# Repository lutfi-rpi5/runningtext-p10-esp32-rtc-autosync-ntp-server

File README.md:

# Running Text P10 ESP32 + RTC + Auto Sync NTP Server

**Detailed Engineering Design (DED) – Embedded System Engineer**

---

## 1. Tentang Sistem

Sistem ini adalah **Running Text LED P10 berbasis ESP32** yang dirancang sebagai papan informasi digital cerdas. Keunggulan utamanya adalah ketahanan terhadap gangguan internet: display tetap menampilkan teks berjalan dan waktu dari **RTC (Real-Time Clock)** meskipun jaringan Wi-Fi tidak tersedia. Ketika koneksi internet kembali, sistem akan **secara otomatis menyinkronkan waktu dari server NTP (Network Time Protocol)** dan menyimpannya ke modul RTC, memastikan akurasi waktu yang tinggi tanpa campur tangan pengguna.

Sistem dibangun dengan pendekatan **non-blocking** pada seluruh operasi (Wi-Fi, NTP, display), sehingga running text tetap berjalan lancar tanpa jeda yang mengganggu. Arsitektur modular memisahkan logika display, RTC, sinkronisasi NTP, dan buzzer ke dalam file terpisah, memudahkan pengembangan dan pemeliharaan.

**Target Aplikasi:**

- Papan informasi kampus, sekolah, atau institusi.
- Display jam digital di ruang publik (lobi, koridor).
- Papan pengumuman di bengkel, laboratorium, atau area produksi.
- Sistem signage mandiri dengan ketergantungan internet minimal.

---

## 2. Identitas Programmer

| **Atribut**         | **Detail**                                                                   |
|---------------------|------------------------------------------------------------------------------|
| **Nama**            | Muhammad Lutfi Nur Anendi                                                    |
| **GitHub**          | [lutfi-rpi5](https://github.com/lutfi-rpi5)                                  |
| **Board Target**    | ESP32 WROOM-32 (ESP32 Dev Module v1.0.6)                                     |
| **Tanggal Rilis**   | 3 April 2026                                                                 |
| **Versi Firmware**  | 1.0.0 (Stable)                                                               |
| **Lisensi**         | MIT                                                                          |

---

## 3. Fitur Sistem

| **Fitur**                           | **Deskripsi**                                                                                                  |
|-------------------------------------|----------------------------------------------------------------------------------------------------------------|
| **Running Text LED P10**            | Mendukung panel P10 *single-color* dengan konfigurasi dimensi yang dapat diatur (`DISPLAYS_ACROSS`, `DISPLAYS_DOWN`). |
| **RTC Offline Mode**                | Waktu tetap akurat menggunakan modul RTC DS1302/DS3231 saat tidak ada internet.                                |
| **Auto Sync NTP Server**            | Sinkronisasi waktu otomatis setiap interval tertentu (default 60 menit) ketika Wi-Fi tersedia.                 |
| **Non-blocking Architecture**       | Semua operasi (Wi-Fi, NTP, display) berjalan tanpa memblokir *main loop*, menjamin running text tetap halus.   |
| **Fallback Otomatis ke RTC**        | Jika NTP gagal atau internet putus, sistem langsung beralih ke RTC tanpa mengganggu tampilan.                  |
| **Scene Management**                | Mendukung dua *scene* utama: **Scene 1 (Running Text)** dan **Scene 2 (Display RTC)** dengan transisi otomatis.|
| **Durasi Tampil RTC Dapat Dikonfigurasi** | Waktu tampil scene RTC dapat diatur dalam milidetik (default 3 menit).                                         |
| **Buzzer Feedback**                 | Indikator suara untuk *boot*, sinkronisasi berhasil, dan *error*.                                              |
| **Konfigurasi Mudah via Kode**      | Semua parameter (SSID, password, zona waktu, kecepatan scroll, dll.) terpusat di file `.ino` dan `.cpp`.       |
| **Modular Code**                    | Pemisahan modul `RunningText`, `RTCAutoSync`, `Buzzer`, dan `virtuabotixRTC` untuk kemudahan *debugging* dan pengembangan. |

---

## 4. Arsitektur Sistem

Diagram blok berikut menggambarkan aliran data dan kontrol utama:

```
+----------------+      +----------------+      +----------------+
|   Internet     |      |   ESP32        |      |   LED Panel    |
|   (NTP Server) |<---->|   (Wi-Fi)      |<---->|   P10          |
+----------------+      +----------------+      +----------------+
                              ^   ^
                              |   |
                              v   v
                         +----------------+
                         |   RTC Module   |
                         |   (DS1302)     |
                         +----------------+
                              ^
                              |
                              v
                         +----------------+
                         |   Buzzer       |
                         |   (Feedback)   |
                         +----------------+
```

**Alur Kerja Sistem:**

1. **ESP32 Boot** – Inisialisasi Serial, Buzzer, RTC, dan Display.
2. **Coba Koneksi Wi-Fi** – Dilakukan secara *non-blocking* setelah *boot delay* (default 0 detik).
3. **Jika Berhasil → Sync NTP** – Waktu dari `pool.ntp.org` diambil, dikonversi ke zona waktu WIB (GMT+7), dan disimpan ke RTC.
4. **Jika Gagal → Gunakan RTC** – Sistem tetap beroperasi dengan waktu yang tersimpan di RTC.
5. **Running Text Berjalan** – Scene teks utama ditampilkan (berulang 1x), lalu beralih ke scene RTC selama durasi tertentu, dan kembali ke scene teks.
6. **Sinkronisasi Berkala** – Setiap interval `ntp_sync_interval` (default 60 menit), sistem kembali mencoba sinkronisasi NTP.

**Penanganan Kegagalan:**

- **Wi-Fi Timeout** – Setelah 60 detik tanpa koneksi, Wi-Fi dimatikan untuk menghemat daya.
- **NTP Failed** – RTC tetap digunakan, dan sinkronisasi dicoba lagi pada interval berikutnya.

---

## 5. Hardware Requirements

| **Komponen**               | **Spesifikasi / Catatan**                                                                   |
|----------------------------|---------------------------------------------------------------------------------------------|
| **ESP32**                  | ESP32 WROOM-32 (disarankan) atau varian ESP32 lain dengan pinout serupa.                    |
| **LED Panel P10**          | *Single-color* (merah/hijau/biru), resolusi 32x16 pixel per panel.                          |
| **RTC Module**             | DS1302 (diuji) atau DS3231 (kompatibel). Pastikan baterai CR2032 terpasang untuk backup.    |
| **Power Supply**           | 5V DC dengan arus cukup (min. 2A untuk 1-3 panel, lebih besar untuk panel lebih banyak).    |
| **Kabel Jumper**           | Male-to-female dan female-to-female untuk koneksi ESP32 ↔ P10 ↔ RTC.                        |
| **Buzzer (Opsional)**      | Buzzer aktif LOW 5V.                                                                        |
| **Konektor**               | Header pin 2.54mm untuk koneksi yang rapi.                                                  |

---

## 6. Software Requirements

| **Software**                | **Versi / Catatan**                                                                                     |
|-----------------------------|---------------------------------------------------------------------------------------------------------|
| **Arduino IDE**             | 1.8.19 atau lebih baru.                                                                                 |
| **ESP32 Board Package**     | **Versi 1.0.6** (wajib). Versi lain mungkin menyebabkan error kompilasi pada library DMD32.             |
| **Library DMD32 v1.0**      | Instal via Library Manager Arduino IDE.                                                                 |
| **Library Bawaan ESP32**    | `WiFi.h`, `time.h`, `SPI.h`, `Wire.h` (sudah termasuk dalam board package).                             |
| **Library Lokal (Include)** | `runningtext.h/cpp`, `rtc_autosync.h/cpp`, `virtuabotixRTC.h/cpp`, `buzzer.h/cpp` (sudah ada di repo).  |
| **Fonts**                   | `SystemFont5x7.h`, `Arial_black_16.h` (termasuk dalam library DMD32).                                   |

---

## 7. Installation

### 7.1 Clone Repository

```bash
git clone https://github.com/lutfi-rpi5/runningtext-p10-esp32-rtc-autosync-ntp-server.git
```
Atau unduh ZIP dari GitHub dan ekstrak.

### 7.2 Install ESP32 Board Package v1.0.6
1. Buka **Arduino IDE** → **File** → **Preferences**.
2. Tambahkan URL berikut ke **Additional Boards Manager URLs**:
```text
https://raw.githubusercontent.com/espressif/arduino-esp32/gh-pages/package_esp32_index.json
```
3. Buka **Tools** → **Board** → **Boards Manager**.
4. Cari **ESP32** by Espressif Systems dan instal **versi 1.0.6**.

### 7.3 Install Library DMD32
1. Buka **Sketch** → **Include Library** → **Manage Libraries**.
2. Cari **DMD32** dan install **versi 1.0**.

### 7.4 Buka Project
1. Buka file `runningtext-p10-esp32-rtc-autosync-ntp-server.ino` di **Arduino IDE**.
2. Pastikan board yang dipilih adalah **ESP32 Dev Module** (atau sesuai board Anda).

### 7.5 Compile & Upload
1. Hubungkan ESP32 ke komputer via USB.
2. Pilih port yang sesuai di **Tools** → **Port**.
3. Klik tombol **Upload**.

---

## 8. Configurations
Seluruh konfigurasi penting terpusat di file utama `.ino` dan file modul terkait. Berikut panduan lengkapnya.

### 8a. Sinkronisasi RTC (NTP Sync Interval)
**Lokasi**: `rtc_autosync.cpp` baris 11-13.

```cpp
const unsigned long ntp_sync_interval = (60 * 60) * 1000;  // 60 menit
const unsigned long ntp_sync_starting_at = (0.1 * 60) * 1000; // 10 detik pertama
```

* `ntp_sync_interval` : Interval sinkronisasi NTP dalam milidetik. Default 1 jam.
* `ntp_sync_starting_at` : Delay awal sebelum sinkronisasi pertama setelah boot. Default 10 detik (untuk memberi waktu koneksi Wi-Fi stabil).

### 8b. Time Zone & Day Offset Setting
**Lokasi**: `rtc_autosync.cpp` baris 9-10.

```cpp
const long gmtOffset_sec = 25200;   // WIB (GMT+7) = 7 * 3600 detik
const int daylightOffset_sec = 0;   // Tidak ada DST di Indonesia
```

* `gmtOffset_sec` : Offset zona waktu dalam detik dari GMT.
    * WIB (GMT+7) = 25200
    * WITA (GMT+8) = 28800
    * WIT (GMT+9) = 32400
* `daylightOffset_sec` : Offset Daylight Saving Time (tidak digunakan di Indonesia).

### 8c. SSID & PASSWORD Setting
**Lokasi**: `rtc_autosync.cpp` baris 8.

```cpp
const char* ssid = "sync-elektro";
const char* password = "12345678";
```
Ganti dengan kredensial Wi-Fi yang tersedia.

### 8d. Jumlah Display Across & Display Down
**Lokasi**: `runningtext.cpp` baris 9.

```cpp
#define DISPLAYS_ACROSS 3   // Jumlah panel horizontal
#define DISPLAYS_DOWN 1     // Jumlah panel vertikal
```
Atur sesuai konfigurasi fisik panel P10 Anda. Sistem akan otomatis menyesuaikan lebar total display (`32 * DISPLAYS_ACROSS` pixel).

### 8e. Ganti Text Utama
**Lokasi**: `runningtext-p10-esp32-rtc-autosync-ntp-server.ino` baris 8-10.

```cpp
String text_utama = "Selamat Datang di Bengkel Jurusan Teknik Elektro | Prodi Teknik Elektronika Politeknik Negeri Sriwijaya Utamakan Keselamatan dan Kesehatan Kerja";
```
Ganti dengan teks yang diinginkan. Gunakan karakter `|` sebagai pemisah jika ingin beberapa bagian teks (tidak memengaruhi animasi, hanya teks biasa).

### 8f. Display Speed
**Lokasi**: `runningtext-p10-esp32-rtc-autosync-ntp-server.ino` baris 12.

```cpp
display.setSpeed(20);
```
* Nilai dalam milidetik, semakin kecil semakin cepat. Rentang tipikal 15–50.

### 8g. Durasi Tampil Scene RTC
**Lokasi**: `runningtext-p10-esp32-rtc-autosync-ntp-server.ino` baris 22-23.

```cpp
display.sceneRTC( tanggal, waktu, (3 * 60) * 1000 ); // 3 menit
```
* Ubah (3 * 60) * 1000 menjadi durasi yang diinginkan dalam milidetik. Contoh:
    * 1 menit = (1 * 60) * 1000
    * 5 menit = (5 * 60) * 1000

---

## 9. Pin Configuration

### 9.1 Panel P10 → ESP32

|**P10 Pin**  |	**ESP32 GPIO** |  **Keterangan**  |
|---------|------------|--------------|
|GND      | GND        |	Ground    |
|OE	      | GPIO 22    |Output Enable |
|A	      | GPIO 19    |Address Line A|
|B	      | GPIO 21	   |Address Line B|
|CLK	  | GPIO 18	   |Clock (Shift Register)|
|LAT (STB)|	GPIO 2	   |Latch / Strobe|
|DR (R1)  | GPIO 23	   |Data Red (untuk panel single-color)|

**Catatan**: Untuk panel *single-color*, hanya gunakan pin **R1** (DR). Pin **G1** (hijau) dan **B1** (biru) tidak digunakan.

### 9.2 RTC (DS1302) → ESP32
|**DS1302 Pin** |	**ESP32 GPIO**  |
|-----------|---------------|
|CLK	    |    GPIO 25    |
|DAT	    |    GPIO 26    |
|RST	    |    GPIO 27    |
|VCC	    |5V (atau 3.3V) |
|GND	    |    GND        |

### 9.3 Buzzer → ESP32
|Buzzer Pin	 | ESP32 GPIO  |
|------------|-------------|
|+ (Positif) |	GPIO 33    |
|- (Negatif) |	GND        |

**Catatan**: Buzzer dikonfigurasi active *LOW* (menyala saat pin diberi logika `LOW`). Jika menggunakan buzzer langsung tanpa relay, ubah logika di `buzzer.cpp` baris 4-5 sesuai komentar.

---

## 10. Struktur Proyek
```text
runningtext-p10-esp32-rtc-autosync-ntp-server/
│
├── runningtext-p10-esp32-rtc-autosync-ntp-server.ino   # Main sketch
├── runningtext.h / .cpp                                # Modul display & scene
├── rtc_autosync.h / .cpp                               # Modul RTC & NTP sync
├── virtuabotixRTC.h / .cpp                             # Library RTC DS1302
├── buzzer.h / .cpp                                     # Modul buzzer
├── fonts/
│   ├── SystemFont5x7.h
│   └── Arial_black_16.h
├── build/                                              # Compiled firmware (opsional)
└── README.md
```

---

## 11. Troubleshooting

| **Masalah**                              | **Solusi**                                                                                                                                                                                                                                                                                                                                                                                                                                                                                                                                                                                                 |
|------------------------------------------|-------------------------------------------------------------------------------------------------------------------------------------------------------------------------------------------------------------------------------------------------------------------------------------------------------------------------------------------------------------------------------------------------------------------------------------------------------------------------------------------------------------------------------------------------------------------------------------------------------------|
| **Display tidak menyala / blank**        | - Periksa koneksi kabel P10 (OE, CLK, LAT, DR).<br>- Pastikan power supply 5V mencukupi (gunakan adaptor eksternal, bukan USB ESP32).                                                                                                                                                                                                                                                                                                                                                                                                                                                                       |
| **Teks berjalan terlalu cepat/lambat**   | Ubah nilai `display.setSpeed()` di file `.ino`. Semakin kecil nilai, semakin cepat.                                                                                                                                                                                                                                                                                                                                                                                                                                                                                                                         |
| **Waktu RTC tidak akurat / reset**       | - Ganti baterai CR2032 pada modul RTC.<br>- Pastikan sinkronisasi NTP berhasil (lihat Serial Monitor).                                                                                                                                                                                                                                                                                                                                                                                                                                                                                                      |
| **Wi-Fi tidak terhubung**                | - Periksa SSID dan password di `rtc_autosync.cpp`.<br>- Pastikan sinyal Wi-Fi cukup kuat.<br>- Tambahkan `delay(5000)` setelah `WiFi.begin()`.                                                                                                                                                                                                                                                                                                                                                                                                                                                              |
| **ESP32 bootloop (restart terus pada saat di Serial Monitor)**       | **Solusi Umum:** <br>- Buka Serial Monitor (baud 115200) dan periksa pesan error terakhir.<br>- Coba *flash* ulang firmware sambil menekan tombol **BOOT**.<br>- Pastikan power supply stabil (3.3V/5V) dan tidak ada korsleting pada pin GPIO.<br>- Hapus flash sepenuhnya dengan `esptool.py erase_flash` lalu upload ulang.<br><br>**Solusi Alternatif (Khusus Windows User – Pembersihan Cache & Instal Ulang Board Package):** <br>1. Buka **Board Manager** di Arduino IDE, cari **ESP32** by Espressif Systems, lalu klik **Remove** untuk menghapus versi yang terpasang (misal v1.0.6).<br>2. Tutup **semua jendela** Arduino IDE yang sedang berjalan.<br>3. Tekan tombol <kbd>Win</kbd> + <kbd>R</kbd>, ketik `%TEMP%` lalu tekan **Enter**. Pilih semua file dan folder (<kbd>Ctrl</kbd> + <kbd>A</kbd>) kemudian hapus permanen dengan <kbd>Shift</kbd> + <kbd>Delete</kbd>.<br>4. Ulangi langkah 3 untuk direktori **`temp`** dan **`PREFETCH`** (ketik masing‑masing pada dialog **Run**).<br>5. **Restart** komputer/laptop.<br>6. Buka kembali Arduino IDE, instal ulang **ESP32 Board Package versi 1.0.6** melalui Board Manager.<br>7. Coba upload ulang sketch. |
| **Kompilasi error "DMD was not declared"** | Pastikan library **DMD32** sudah terinstal. Jika tetap error, coba hapus dan instal ulang library.                                                                                                                                                                                                                                                                                                                                                                                                                                                                                                           |
| **ESP32 tidak terdeteksi di Arduino IDE** | - Tekan tombol BOOT saat uploading.<br>- Instal driver USB-to-Serial (CP210x atau CH340).                                                                                                                                                                                                                                                                                                                                                                                                                                                                                                                    |

## 12. Pengembangan Lebih Lanjut
* **OTA Update**: Tambahkan fitur Over-the-Air untuk update firmware via Wi-Fi.
* **Multi-Scene**: Tambahkan lebih banyak scene (misal: suhu, kelembaban, atau informasi dari sensor).
* **Web Config**: Buat portal web sederhana untuk mengubah teks dan pengaturan tanpa recompile.
* **E-paper / OLED**: Integrasi display sekunder untuk informasi status sistem.

---

## 13. Kontribusi
Kontribusi dalam bentuk pull request atau issue sangat diterima. Pastikan kode mengikuti gaya penulisan yang konsisten dan terdokumentasi dengan baik.

## 14. Lisensi
Proyek ini dilisensikan di bawah **MIT License**. Silakan gunakan, modifikasi, dan distribusikan sesuai kebutuhan.

**Dokumentasi ini disusun berdasarkan analisis menyeluruh terhadap kode sumber, struktur proyek, dan best practice _embedded system engineering_. Untuk pertanyaan lebih lanjut, silakan buka _issue_ di repositori GitHub.**

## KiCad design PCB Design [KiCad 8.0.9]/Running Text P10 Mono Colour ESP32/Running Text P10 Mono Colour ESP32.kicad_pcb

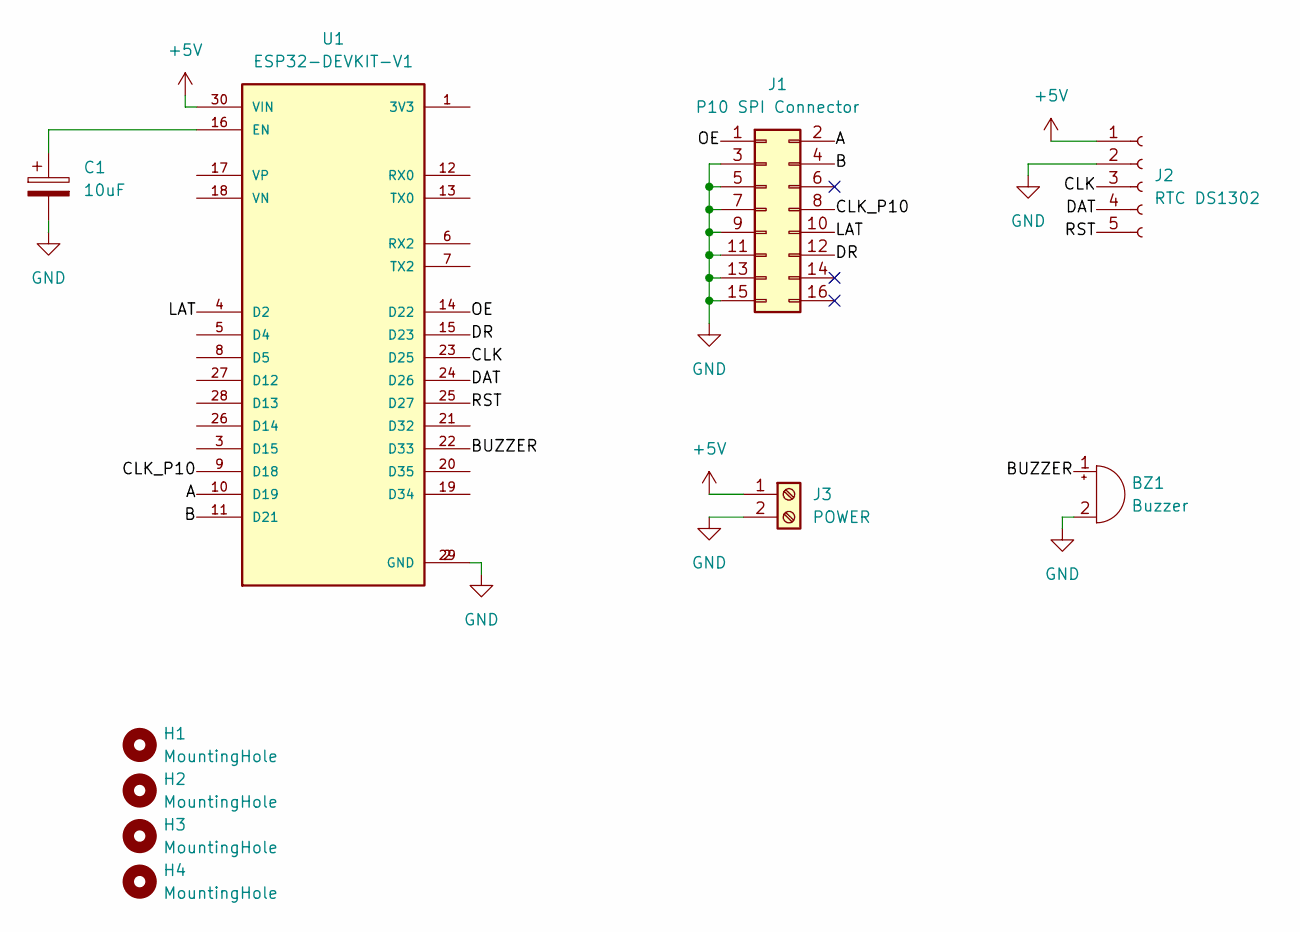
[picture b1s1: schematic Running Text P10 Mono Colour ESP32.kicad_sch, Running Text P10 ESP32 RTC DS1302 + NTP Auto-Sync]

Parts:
BZ1: Buzzer; Buzzer_12x9.5RM7.6
C1: 10uF; CP_Radial_D5.0mm_P2.50mm
H1, H2, H3, H4: MountingHole; MountingHole_3mm
J1: P10 SPI Connector; IDC-Header_2x08_P2.54mm_Vertical
J2: RTC DS1302; PinHeader_1x05_P2.54mm_Vertical
J3: POWER; TerminalBlock_RND_205-00232_1x02_P5.08mm_Horizontal
U1: ESP32-DEVKIT-V1; ESP32_DEVKIT_V1; PARTREV N/A

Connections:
+5V: J2.1, J3.1, U1.30 (VIN)
/A: J1.2, U1.10 (D19)
/B: J1.4, U1.11 (D21)
/BUZZER: BZ1.1 (+), U1.22 (D33)
/CLK: J2.3, U1.23 (D25)
/CLK_P10: J1.8, U1.9 (D18)
/DAT: J2.4, U1.24 (D26)
/DR: J1.12, U1.15 (D23)
/LAT: J1.10, U1.4 (D2)
/OE: J1.1, U1.14 (D22)
/RST: J2.5, U1.25 (D27)
GND: BZ1.2 (-), C1.2, J1.3, J1.5, J1.7, J1.9, J1.11, J1.13, J1.15, J2.2, J3.2, U1.2 (GND), U1.29 (GND)
unnamed: C1.1, U1.16 (EN)

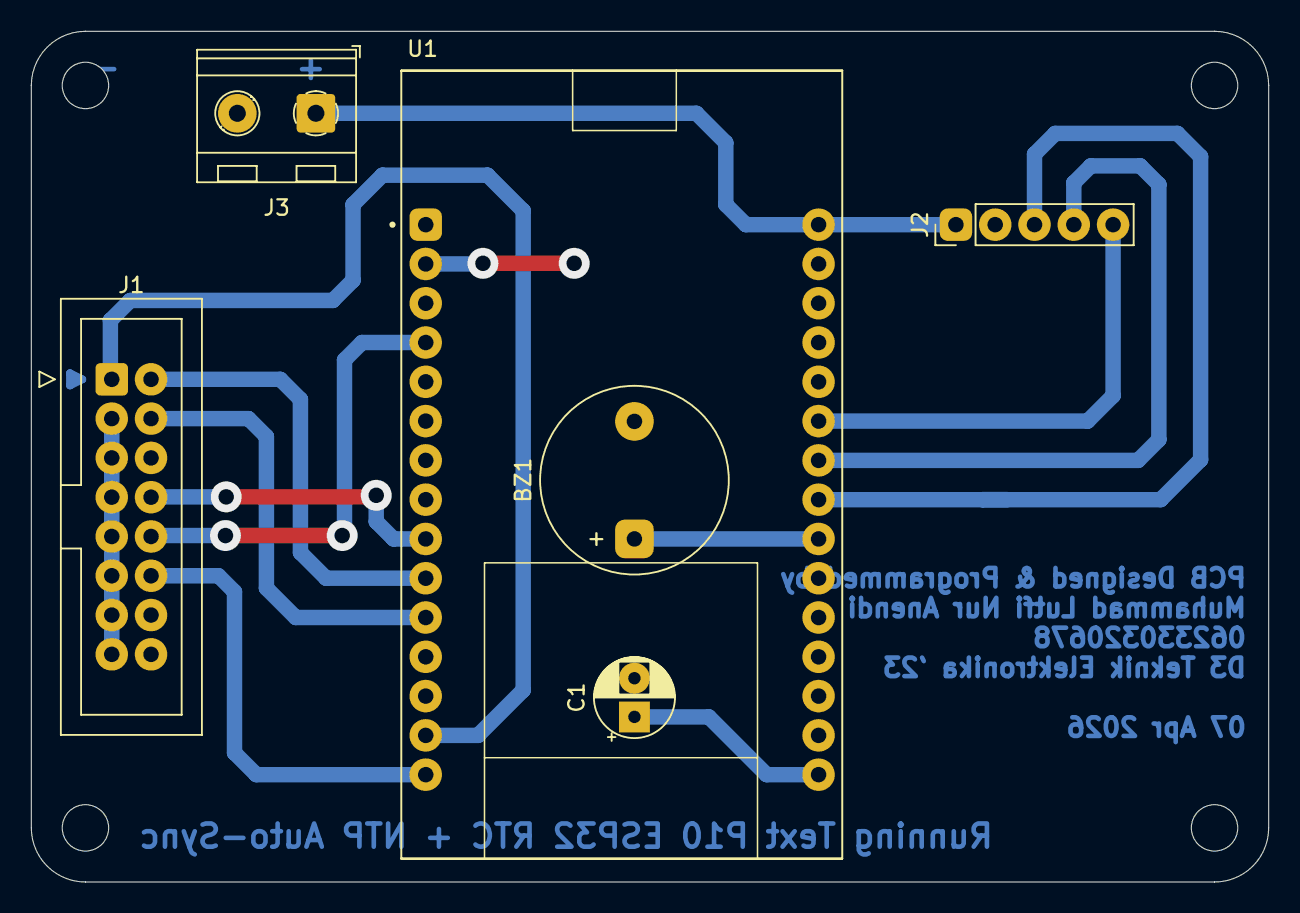
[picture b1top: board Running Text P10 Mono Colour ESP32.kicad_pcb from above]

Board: 2 copper layers, 80.0 x 55.0 mm, 10 parts (0 on the bottom side), 13 nets.

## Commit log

2026-04-04 init & up project to github
2026-04-04 modify README.md
2026-04-16 release version
2026-04-16 refactor
2026-04-16 create documentation
2026-04-16 Add MIT License to the project
2026-04-16 build firmware Elektronika & Telekomunikasi
2026-04-17 add assets
2026-04-17 Modified README.md
2026-04-17 add PCB Design KiCad 8.0.9
2026-04-17 add Schematic and PCB Print Out Sheet KiCad 8.0.9
